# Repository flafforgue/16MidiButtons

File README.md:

# 16MidiButtons
 16 Buttons Midi Controler<br><br>
  16 Buttons<br>
  4 Pots<br>
  1306 Oled 1,3" display<br>
 <br>
 Unsing :<br>
 - Ardunin Micro<br>
 - 2 x 74HC595 for extention of Number Led<br>
 - 2 x 74HC165 for Buttons<br>
 <br> 
 ToDo:<br>
 - realy send Midi message, procedure prepared but empty ;)<br>
 - pots <br>
 - eeprom config save<br>
 - enhanced demo mode<br>
 - Software to Configure on PC<br>
 <br>
 Project Ongoing :<br>
 v0.11 add control switch mode ( see code )<br> 
 V0.10 setup            - ok<br>
 V0.06 Test menus       - ok<br>
 V0.05 test Encoder     - ok<br>
 V0.04 test SSD1306     - ok<br>
 V0.03 test 74HC165 Lib - ok<br>
 V0.02 test 74HC595 Lib - ok<br>
 <br><br>
 Adding Aplication in Lazarys/FreePascal to edit Demo parterns
<br>

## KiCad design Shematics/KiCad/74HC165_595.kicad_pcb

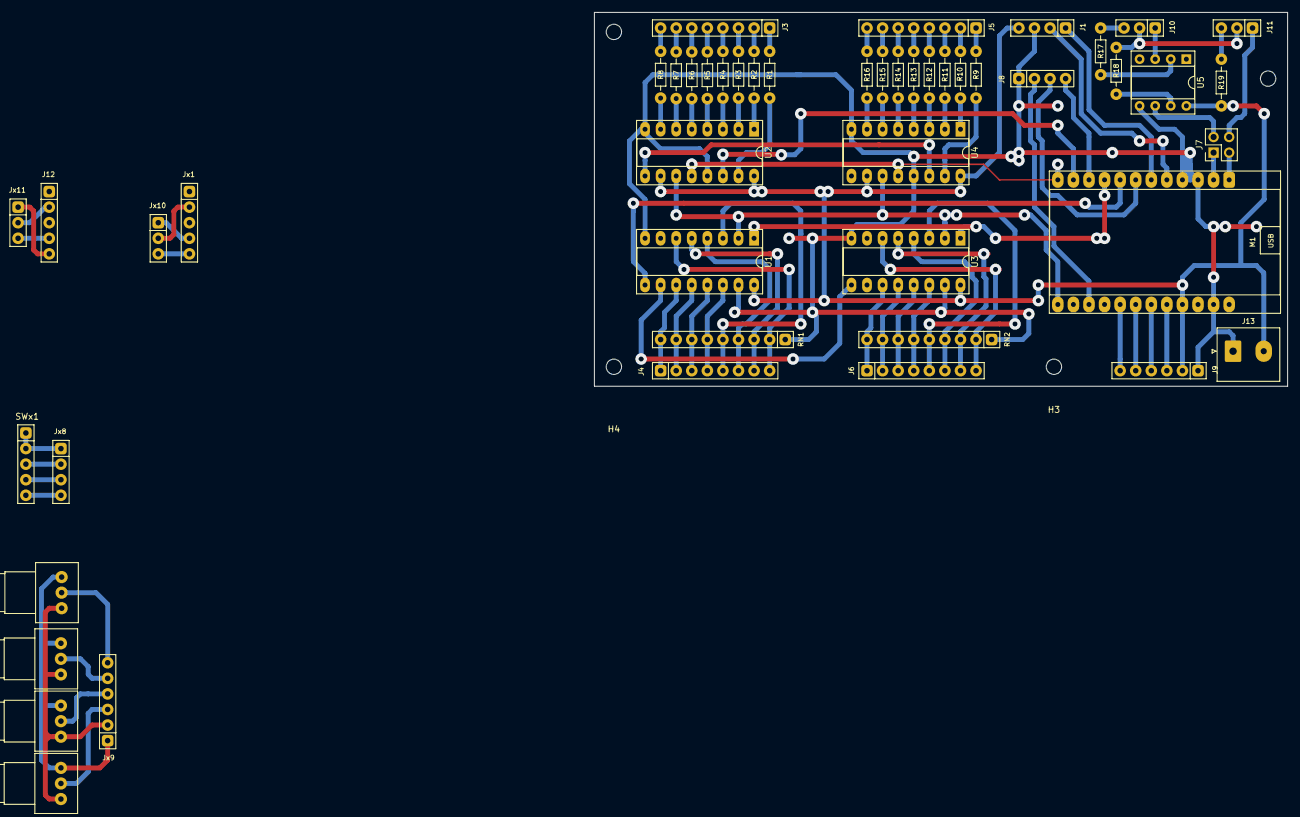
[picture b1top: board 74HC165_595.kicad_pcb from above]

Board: 2 copper layers, 113.0 x 61.0 mm, 53 parts (0 on the bottom side), 91 nets.

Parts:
H1, H2, H3, H4: MountingHole; MountingHole_2.5mm
J1: Oled; Con_1x04_P2.54mm
J3, J4, J5, J6: Conn_01x08; Con_1x08_P2.54mm
J7: Conn_02x02_Odd_Even; PinHeader_2x02_P2.54mm_Vertical
J8: Conn_01x04; Con_1x04_P2.54mm
J9: Conn_01x06; Con_1x06_P2.54mm
J10: Midi-In; Con_1x03_P2.54mm
J11: Midi-Out; Con_1x03_P2.54mm
J12: MIDI OUT; Con_1x05_P2.54mm
J13: Conn_01x02; Vis_1x02_P5.00
Jx1: MIDI IN; Con_1x05_P2.54mm
Jx8: Conn_01x04; Con_1x04_P2.54mm
Jx9: Conn_01x06; Con_1x06_P2.54mm
Jx10: Midi-In; Con_1x03_P2.54mm
Jx11: Midi-Out; Con_1x03_P2.54mm
M1: Arduino-Pro-Micro-Module; Arduino-Pro-Micro-DIP-24
R1, R2, R3, R4, R5, R6, R7, R8, R9, R10, R11, R12, R13, R14, R15, R16: 0; Rx
R17, R19: 220; Rx
R18: 4k7; Rx
RN1, RN2: R_Network08_US; Con_1x09_P2.54mm
RVx0, RVx1, RVx2, RVx3: 10k; Pot_APLS_Single
SWx1: Rotary_Encoder_Switch; Encoder
U1, U3: 74HC165; DIP-16_W7.62mm_Socket_LongPads
U2, U4: 74HC595; DIP-16_W7.62mm_Socket_LongPads
U5: 6N138; DIP-8_W7.62mm_Socket

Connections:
+5V: J1.4, J9.2, J13.2, M1.21, R19.1, U1.16, U2.10, U2.16, U3.16, U4.10, U4.16, U5.8
/CS_In: M1.9, U1.1, U3.1
/Clk: M1.13, U1.2, U2.11, U3.2, U4.11
/Din: M1.8, U1.9
/Dout: M1.11, U2.14
/Latch_Out: M1.12, U2.12, U4.12
GND: J1.3, J8.1, J9.1, J10.2, J11.2, J13.1, M1.3, M1.4, M1.23, R18.1, RN1.1, RN2.1, U1.8, U1.15, U2.8, U2.13, U3.8, U3.15, U4.8, U4.13, U5.5
unnamed: J1.1, M1.6
unnamed: J1.2, M1.5
unnamed: J3.1, R1.1
unnamed: J3.2, R2.1
unnamed: J3.3, R3.1
unnamed: J3.4, R4.1
unnamed: J3.5, R5.1
unnamed: J3.6, R6.1
unnamed: J3.7, R7.1
unnamed: J3.8, R8.1
unnamed: J4.1, RN1.9, U1.11
unnamed: J4.2, RN1.8, U1.12
unnamed: J4.3, RN1.7, U1.13
unnamed: J4.4, RN1.6, U1.14
unnamed: J4.5, RN1.5, U1.3
unnamed: J4.6, RN1.4, U1.4
unnamed: J4.7, RN1.3, U1.5
unnamed: J4.8, RN1.2, U1.6
unnamed: J5.1, R9.1
unnamed: J5.2, R10.1
unnamed: J5.3, R11.1
unnamed: J5.4, R12.1
unnamed: J5.5, R13.1
unnamed: J5.6, R14.1
unnamed: J5.7, R15.1
unnamed: J5.8, R16.1
unnamed: J6.1, RN2.9, U3.11
unnamed: J6.2, RN2.8, U3.12
unnamed: J6.3, RN2.7, U3.13
unnamed: J6.4, RN2.6, U3.14
unnamed: J6.5, RN2.5, U3.3
unnamed: J6.6, RN2.4, U3.4
unnamed: J6.7, RN2.3, U3.5
unnamed: J6.8, RN2.2, U3.6
unnamed: J7.1, M1.2
unnamed: J7.2, U5.6
unnamed: J7.3, M1.1
unnamed: J8.2, M1.15
unnamed: J8.3, M1.7
unnamed: J8.4, M1.10
unnamed: J9.3, M1.20
unnamed: J9.4, M1.19
unnamed: J9.5, M1.18
unnamed: J9.6, M1.17
unnamed: J10.1, U5.3
unnamed: J10.3, R17.2
unnamed: J7.4, J11.1
unnamed: J11.3, R19.2
unnamed: J12.2, Jx11.2
unnamed: J12.4, Jx11.3
unnamed: J12.5, Jx11.1
unnamed: Jx1.2, Jx10.2
unnamed: Jx1.4, Jx10.1
unnamed: Jx1.5, Jx10.3
unnamed: Jx8.1, SWx1.C, SWx1.S2
unnamed: Jx8.2, SWx1.S1
unnamed: Jx8.3, SWx1.B
unnamed: Jx8.4, SWx1.A
unnamed: Jx9.1, RVx0.1, RVx1.1, RVx2.1, RVx3.1
unnamed: Jx9.2, RVx0.3, RVx1.3, RVx2.3, RVx3.3
unnamed: Jx9.3, RVx0.2
unnamed: Jx9.4, RVx1.2
unnamed: Jx9.5, RVx2.2
unnamed: Jx9.6, RVx3.2
unnamed: R1.2, U2.15
unnamed: R2.2, U2.1
unnamed: R3.2, U2.2
unnamed: R4.2, U2.3
unnamed: R5.2, U2.4
unnamed: R6.2, U2.5
unnamed: R7.2, U2.6
unnamed: R8.2, U2.7
unnamed: R9.2, U4.15
unnamed: R10.2, U4.1
unnamed: R11.2, U4.2
unnamed: R12.2, U4.3
unnamed: R13.2, U4.4
unnamed: R14.2, U4.5
unnamed: R15.2, U4.6
unnamed: R16.2, U4.7
unnamed: R17.1, U5.2
unnamed: R18.2, U5.7
unnamed: U1.10, U3.9
unnamed: U2.9, U4.14

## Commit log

2023-05-02 74HC165 tested
2023-05-06 Demo Editor
2023-05-08 schematic update
